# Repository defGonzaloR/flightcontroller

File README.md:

# flightcontroller

During a time of growing interest in embedded systems, and currently within flight systems, I designed this simple flight controller. 
Its design consists of a 5V input from a battery that will be used to power the rest of the board. From here it's outputted to 4 actuators, connected through JST connectors. The 5V is stepped down to 3.3V through an LDO and to the digital half of the board. 
The brain of the board is an STM32103C8T6, a selection I took from a STM32 blue pill design, which was commonly referred to for techniques withing this board. The main peripherals on this board are the barometer and IMU, which will give information about the orientation and direction of the flight system. The STM32 also controls the PWM driver responsible for actuator control. A design technique I tried to implement here was trace length matching for an alignment of the signals between the four actuators. The STM32 is also connected to a NEO 9M gps module with an external antenna, something I've never worked with before but am really excited to learn to setup. There's two programming/debugging inputs, being the SWD and USB-C ports. I also added a USART header for later convenience should I want to add anything external to both the STM32 and GPS module. I also provided boot mode and power connection switches. 
This is my most complex PCB yet, and once it arrives I hope to learn even more through debugging and assembly, as well as testing with a model plane.
# Schematic

# Layout

# 3D View

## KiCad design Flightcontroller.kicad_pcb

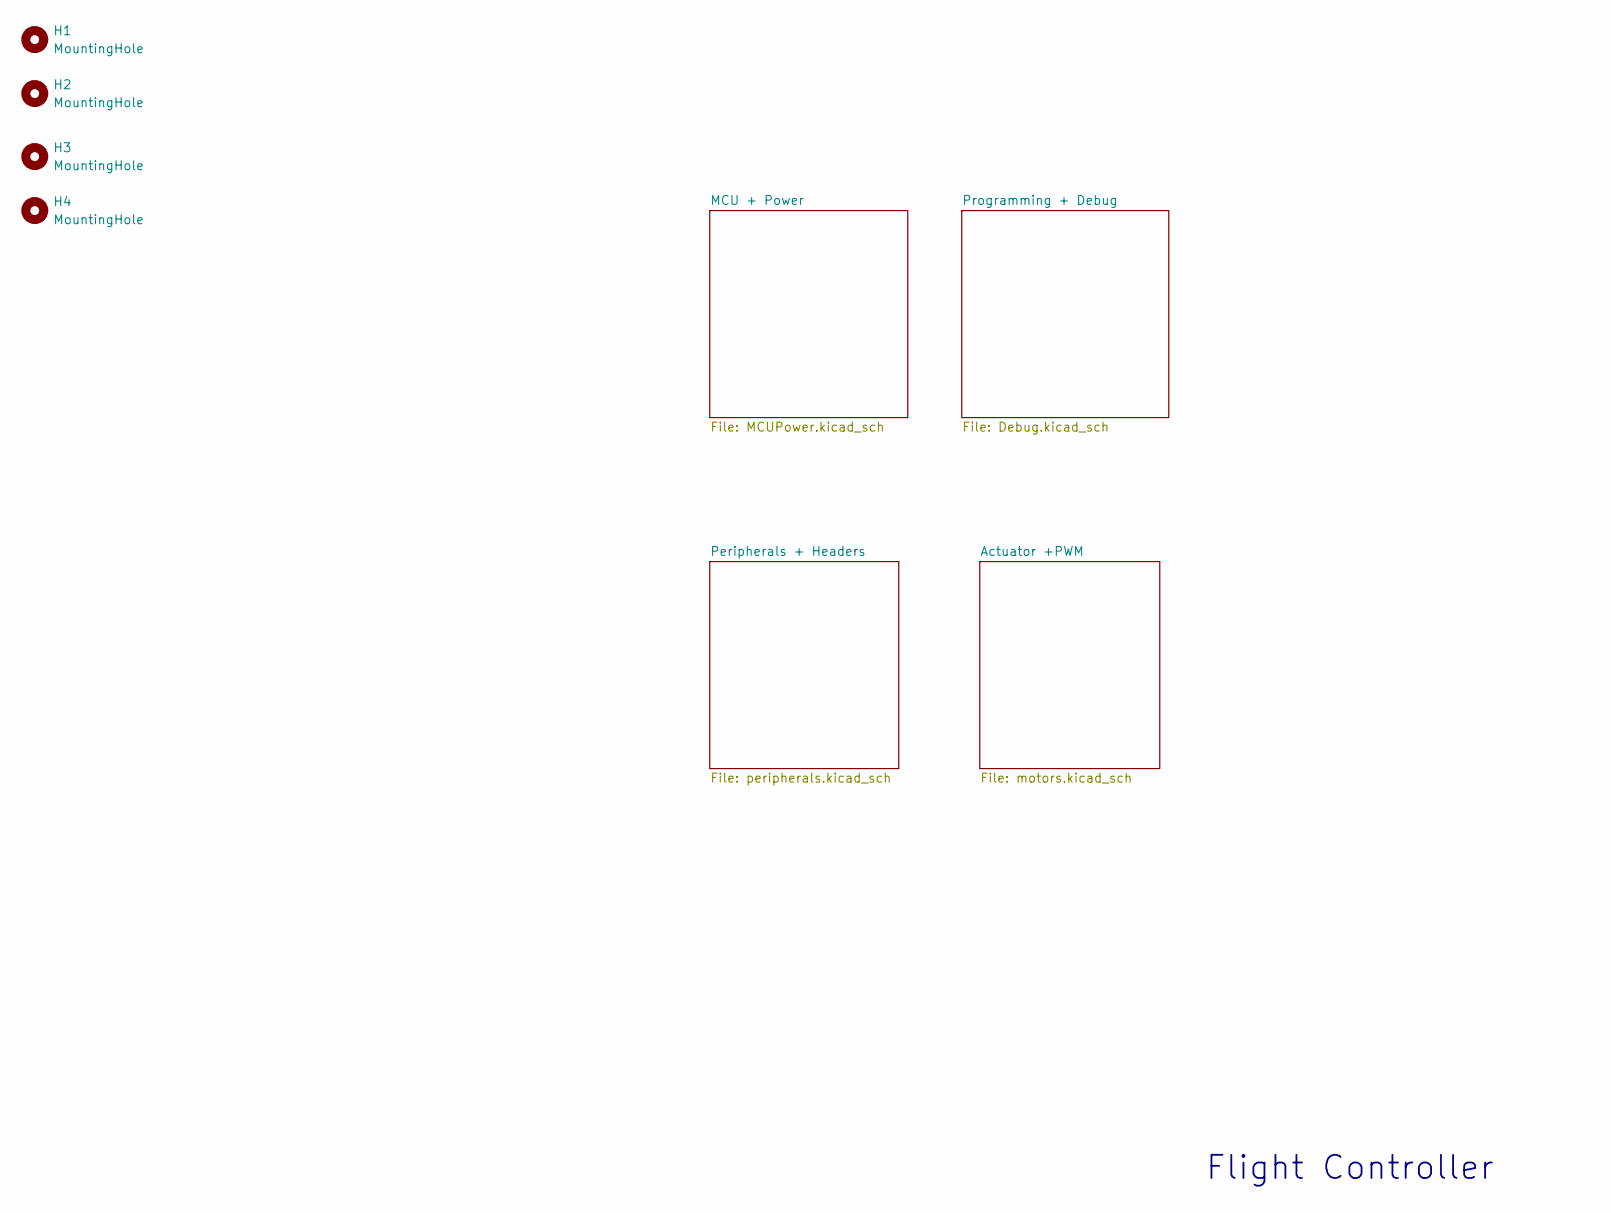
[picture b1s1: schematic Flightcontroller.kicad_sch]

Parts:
H1, H2, H3, H4: MountingHole; MountingHole_2.2mm_M2

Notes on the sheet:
Flight Controller

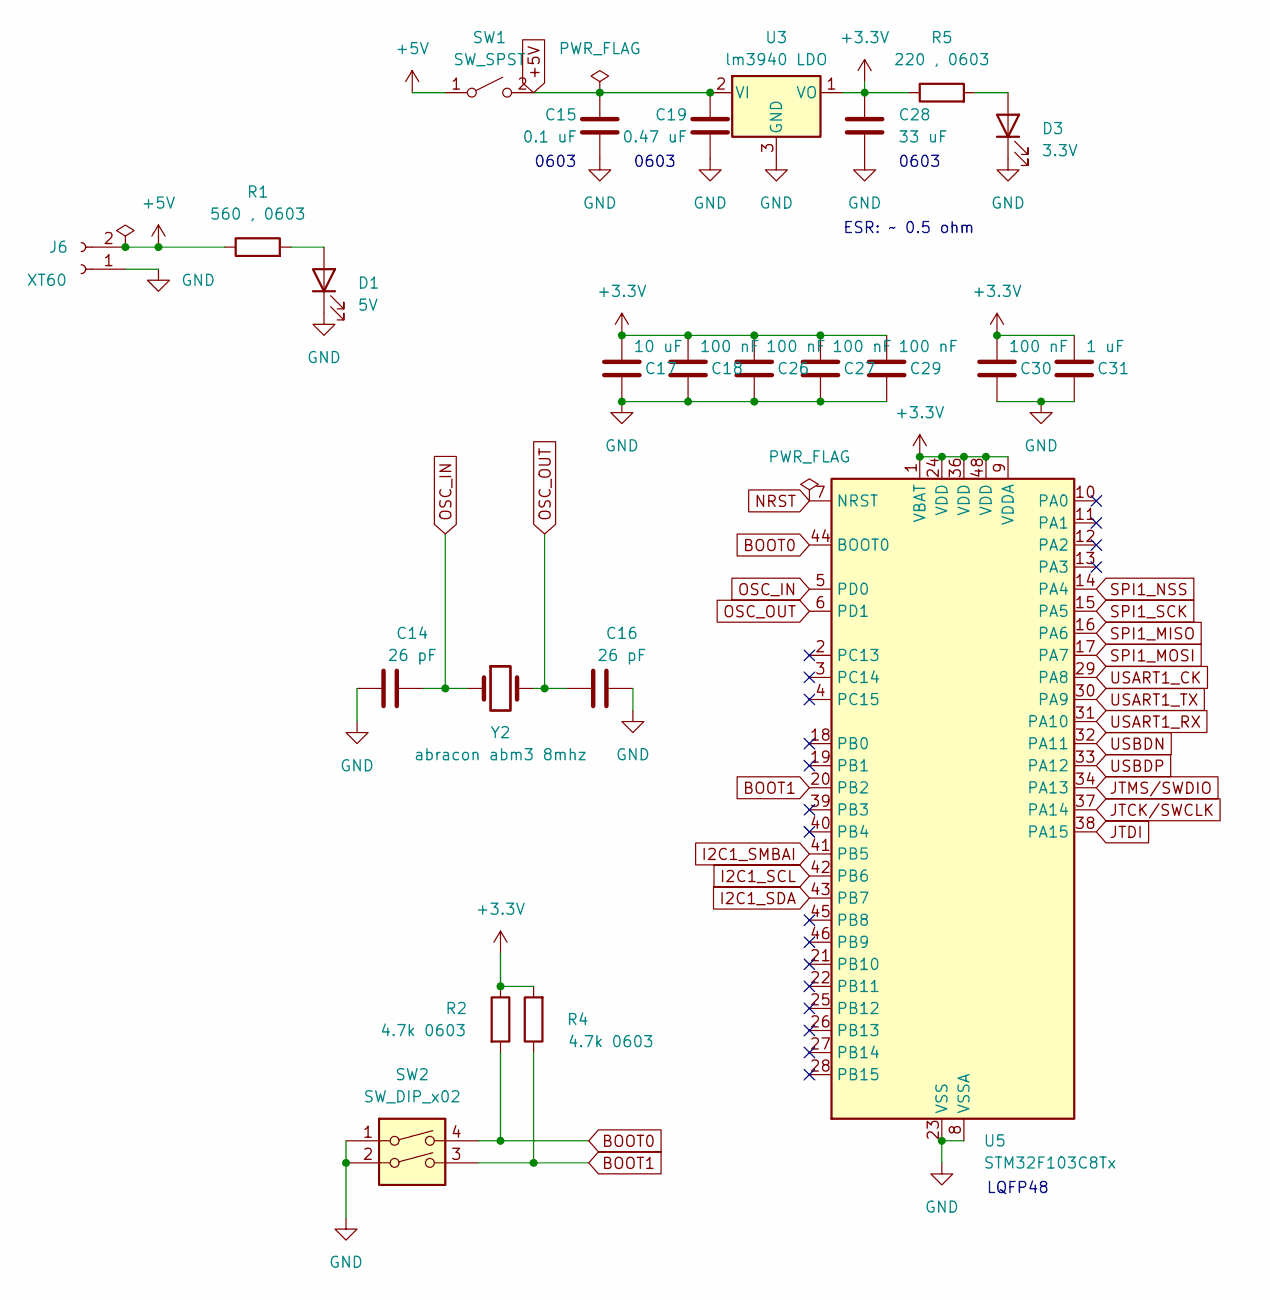
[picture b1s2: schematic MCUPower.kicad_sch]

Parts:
C14, C16: 26 pF; C_0201_0603Metric
C15: 0.1 uF; C_0201_0603Metric
C17: 10 uF; C_0201_0603Metric
C18, C26, C27, C29, C30: 100 nF; C_0201_0603Metric
C19: 0.47 uF; C_0201_0603Metric
C28: 33 uF; C_0201_0603Metric
C31: 1 uF; C_0201_0603Metric
D1: 5V; LED_0201_0603Metric
D3: 3.3V; LED_0201_0603Metric
J6: XT60; AMASS_XT60PW-M_1x02_P7.20mm_Horizontal
R1: 560 , 0603; R_0201_0603Metric
R2, R4: 4.7k 0603; R_0201_0603Metric
R5: 220 , 0603; R_0201_0603Metric
SW1: SW_SPST; SW_DIP_SPSTx01_Slide_9.78x4.72mm_W8.61mm_P2.54mm
SW2: SW_DIP_x02; SW_DIP_SPSTx02_Slide_9.78x7.26mm_W8.61mm_P2.54mm
U3: lm3940 LDO; SOT-23
U5: STM32F103C8Tx; LQFP-48_7x7mm_P0.5mm
Y2: abracon abm3 8mhz; Crystal_SMD_Abracon_ABM3-2Pin_5.0x3.2mm

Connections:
+3.3V: C17.1, C18.1, C26.1, C27.1, C28.1, C29.1, C30.1, C31.1, R2.1, R4.2, R5.1, U3.1 (VO), U5.1 (VBAT), U5.9 (VDDA), U5.24 (VDD), U5.36 (VDD), U5.48 (VDD); also elsewhere on the board
+5V: C15.1, C19.1, J6.2, R1.1, SW1.1 (A), SW1.2 (B), U3.2 (VI); also elsewhere on the board
BOOT0: R2.2, SW2.4, U5.44 (BOOT0)
BOOT1: R4.1, SW2.3, U5.20 (PB2)
GND: C14.1, C15.2, C16.2, C17.2, C18.2, C19.2, C26.2, C27.2, C28.2, C29.2, C30.2, C31.2, D1.1 (K), D3.1 (K), J6.1, SW2.1, SW2.2, U3.3 (GND), U5.8 (VSSA), U5.23 (VSS), U5.35 (VSS), U5.47 (VSS); also elsewhere on the board
I2C1_SCL: U5.42 (PB6); also elsewhere on the board
I2C1_SDA: U5.43 (PB7); also elsewhere on the board
I2C1_SMBAI: U5.41 (PB5)
JTCK/SWCLK: U5.37 (PA14); also elsewhere on the board
JTDI: U5.38 (PA15)
JTMS/SWDIO: U5.34 (PA13); also elsewhere on the board
NRST: U5.7 (NRST)
unnamed: D1.2 (A), R1.2
unnamed: D3.2 (A), R5.2
OSC_IN: C14.2, U5.5 (PD0), Y2.1
OSC_OUT: C16.1, U5.6 (PD1), Y2.2
SPI1_MISO: U5.16 (PA6)
SPI1_MOSI: U5.17 (PA7)
SPI1_NSS: U5.14 (PA4)
SPI1_SCK: U5.15 (PA5)
USART1_CK: U5.29 (PA8)
USART1_RX: U5.31 (PA10); also elsewhere on the board
USART1_TX: U5.30 (PA9); also elsewhere on the board
USBDN: U5.32 (PA11); also elsewhere on the board
USBDP: U5.33 (PA12); also elsewhere on the board

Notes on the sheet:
LQFP48
ESR: ~ 0.5 ohm
0603

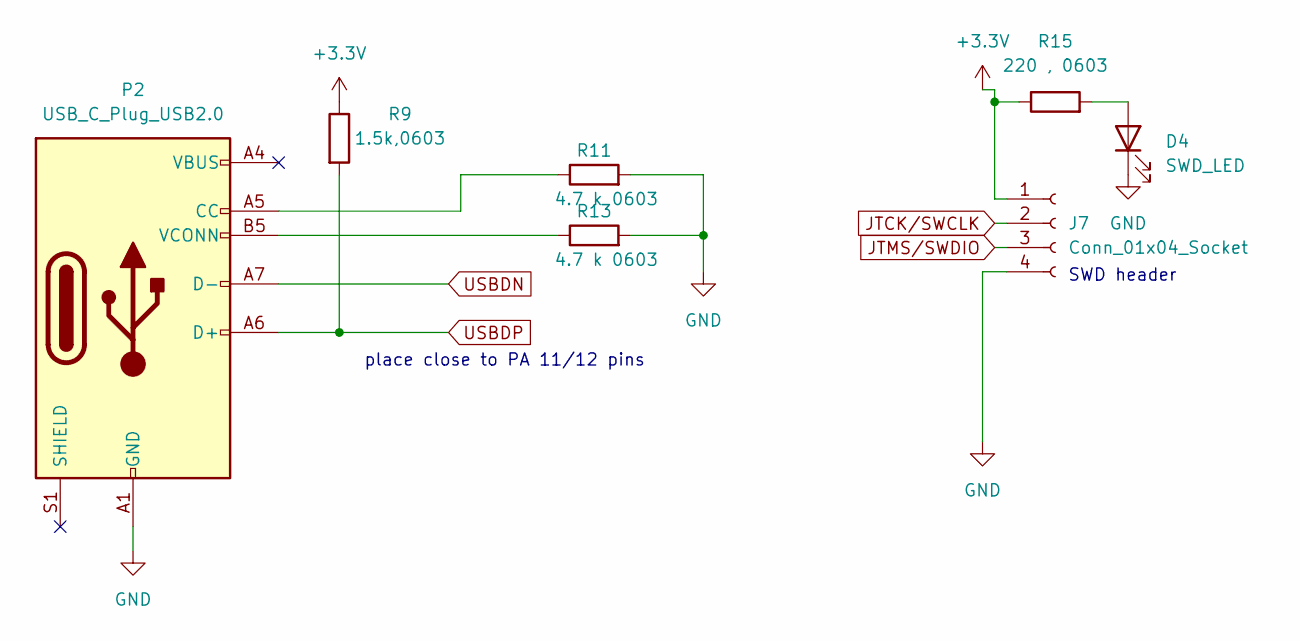
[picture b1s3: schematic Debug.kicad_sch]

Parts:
D4: SWD_LED; LED_0201_0603Metric
J7: Conn_01x04_Socket; JST_EH_B4B-EH-A_1x04_P2.50mm_Vertical
P2: USB_C_Plug_USB2.0; USB_C_Receptacle_GCT_USB4105-xx-A_16P_TopMnt_Horizontal
R9: 1.5k,0603; R_0201_0603Metric
R11, R13: 4.7 k 0603; R_0201_0603Metric
R15: 220 , 0603; R_0201_0603Metric

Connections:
+3.3V: J7.1, R9.1, R15.1; also elsewhere on the board
GND: D4.1 (K), J7.4, P2.A1 (GND), P2.A12 (GND), P2.B1 (GND), P2.B12 (GND), R11.2, R13.2; also elsewhere on the board
JTCK/SWCLK: J7.2; also elsewhere on the board
JTMS/SWDIO: J7.3; also elsewhere on the board
unnamed: D4.2 (A), R15.2
unnamed: P2.A5 (CC), R11.1
unnamed: P2.B5 (VCONN), R13.1
USBDN: P2.A7 (D-); also elsewhere on the board
USBDP: P2.A6 (D+), R9.2; also elsewhere on the board

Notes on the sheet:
place close to PA 11/12 pins
SWD header

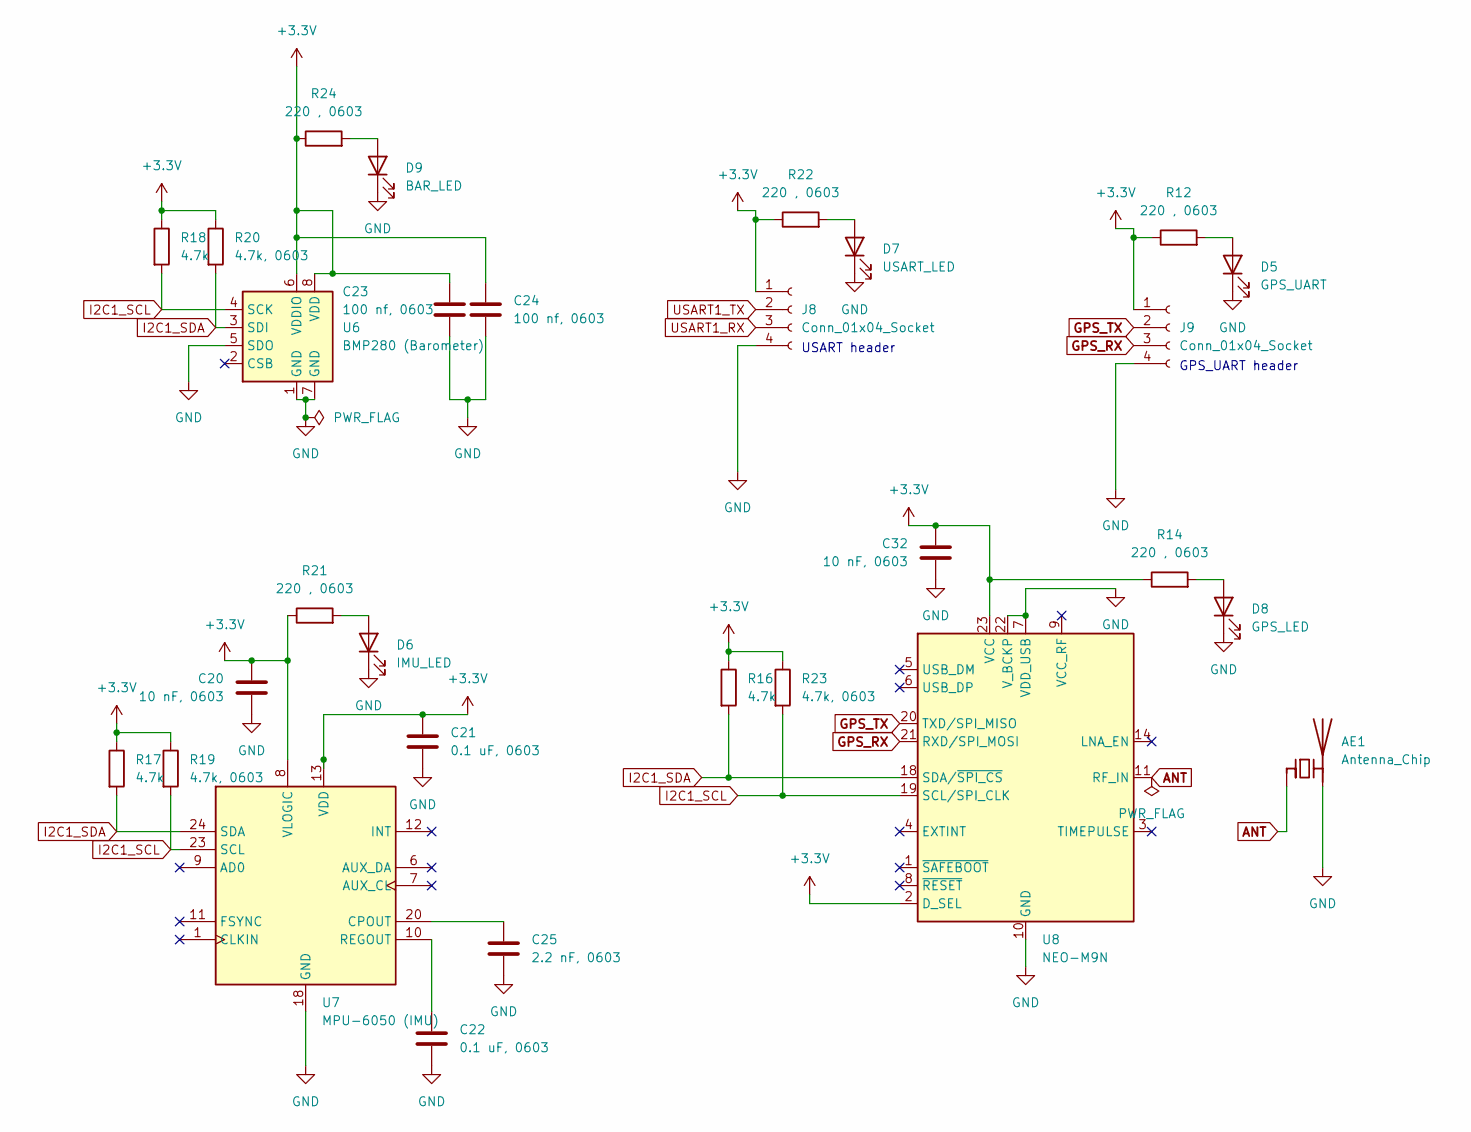
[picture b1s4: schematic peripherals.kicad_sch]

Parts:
AE1: Antenna_Chip; SMA_Amphenol_132134-11_Vertical
C20, C32: 10 nF, 0603; C_0201_0603Metric
C21, C22: 0.1 uF, 0603; C_0201_0603Metric
C23, C24: 100 nf, 0603; C_0201_0603Metric
C25: 2.2 nF, 0603; C_0201_0603Metric
D5: GPS_UART; LED_0201_0603Metric
D6: IMU_LED; LED_0201_0603Metric
D7: USART_LED; LED_0201_0603Metric
D8: GPS_LED; LED_0201_0603Metric
D9: BAR_LED; LED_0201_0603Metric
J8, J9: Conn_01x04_Socket; JST_EH_B4B-EH-A_1x04_P2.50mm_Vertical
R12, R14, R21, R22, R24: 220 , 0603; R_0201_0603Metric
R16, R17, R18: 4.7k; R_0201_0603Metric
R19, R20, R23: 4.7k, 0603; R_0201_0603Metric
U6: BMP280 (Barometer); Bosch_LGA-8_2x2.5mm_P0.65mm_ClockwisePinNumbering
U7: MPU-6050 (IMU); InvenSense_QFN-24_4x4mm_P0.5mm
U8: NEO-M9N; ublox_NEO

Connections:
+3.3V: C20.1, C21.1, C23.1, C24.1, C32.1, J8.1, J9.1, R12.1, R14.1, R16.1, R17.1, R18.1, R19.1, R20.1, R21.1, R22.1, R23.1, R24.1, U6.6 (VDDIO), U6.8 (VDD), U7.8 (VLOGIC), U7.13 (VDD), U8.2 (D_SEL), U8.23 (VCC); also elsewhere on the board
ANT: AE1.1 (FEED), U8.11 (RF_IN)
GND: AE1.2 (PCB_Trace), C20.2, C21.2, C22.2, C23.2, C24.2, C25.2, C32.2, D5.1 (K), D6.1 (K), D7.1 (K), D8.1 (K), D9.1 (K), J8.4, J9.4, U6.1 (GND), U6.5 (SDO), U6.7 (GND), U7.18 (GND), U8.7 (VDD_USB), U8.10 (GND), U8.12 (GND), U8.13 (GND), U8.22 (V_BCKP), U8.24 (GND); also elsewhere on the board
GPS_RX: J9.3, U8.21 (RXD/SPI_MOSI)
GPS_TX: J9.2, U8.20 (TXD/SPI_MISO)
I2C1_SCL: R18.2, R19.2, R23.2, U6.4 (SCK), U7.23 (SCL), U8.19 (SCL/SPI_CLK); also elsewhere on the board
I2C1_SDA: R16.2, R17.2, R20.2, U6.3 (SDI), U7.24 (SDA), U8.18 (SDA/~SPI_CS); also elsewhere on the board
unnamed: D5.2 (A), R12.2
unnamed: D6.2 (A), R21.2
unnamed: D7.2 (A), R22.2
unnamed: D8.2 (A), R14.2
unnamed: D9.2 (A), R24.2
unnamed: C25.1, U7.20 (CPOUT)
unnamed: C22.1, U7.10 (REGOUT)
USART1_RX: J8.3; also elsewhere on the board
USART1_TX: J8.2; also elsewhere on the board

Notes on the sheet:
GPS_UART header
USART header

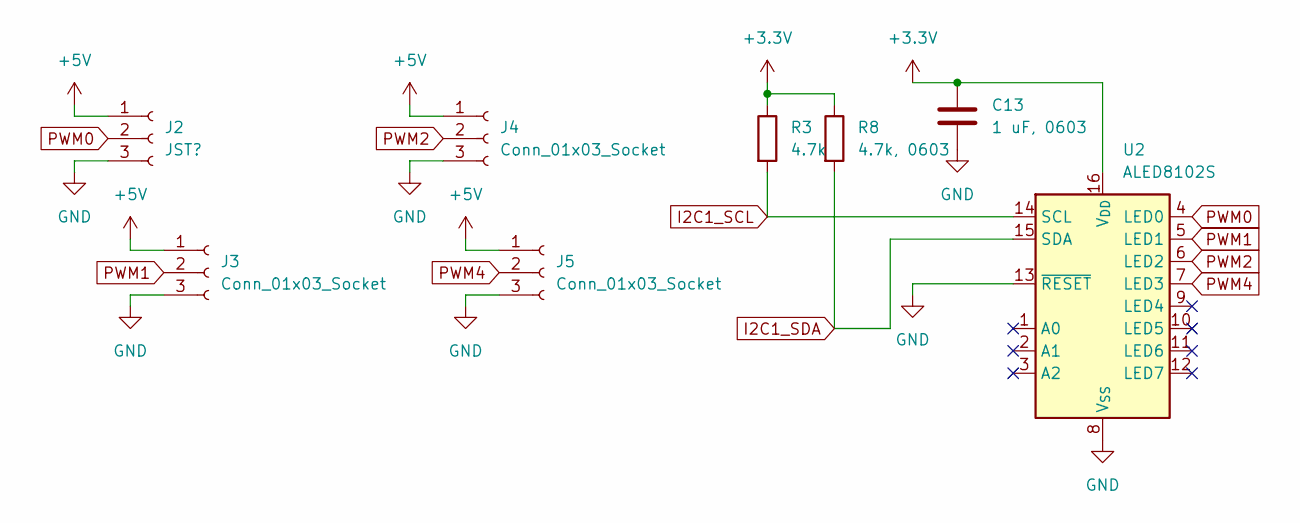
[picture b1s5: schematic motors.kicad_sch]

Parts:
C13: 1 uF, 0603; C_0201_0603Metric
J2: JST?; JST_EH_B3B-EH-A_1x03_P2.50mm_Vertical
J3, J4, J5: Conn_01x03_Socket; JST_EH_B3B-EH-A_1x03_P2.50mm_Vertical
R3: 4.7k; R_0201_0603Metric
R8: 4.7k, 0603; R_0201_0603Metric
U2: ALED8102S; TSSOP-16_4.4x5mm_P0.65mm

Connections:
+3.3V: C13.1, R3.1, R8.1, U2.16 (V_{DD}); also elsewhere on the board
+5V: J2.1, J3.1, J4.1, J5.1; also elsewhere on the board
GND: C13.2, J2.3, J3.3, J4.3, J5.3, U2.8 (V_{SS}), U2.13 (~RESET); also elsewhere on the board
I2C1_SCL: R3.2, U2.14 (SCL); also elsewhere on the board
I2C1_SDA: R8.2, U2.15 (SDA); also elsewhere on the board
PWM0: J2.2, U2.4 (LED0)
PWM1: J3.2, U2.5 (LED1)
PWM2: J4.2, U2.6 (LED2)
PWM4: J5.2, U2.7 (LED3)

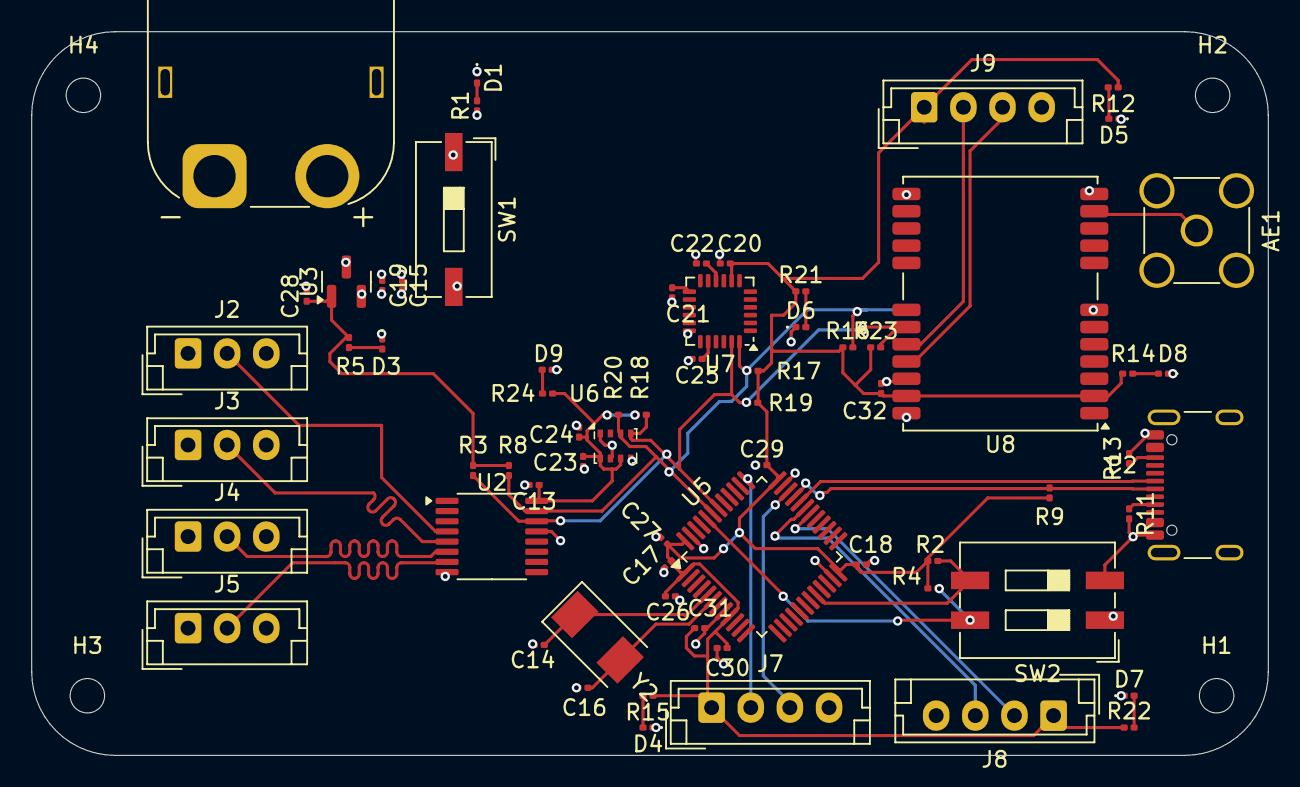
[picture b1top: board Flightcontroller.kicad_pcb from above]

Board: 4 copper layers, 79.0 x 46.2 mm, 72 parts (0 on the bottom side), 34 nets.
